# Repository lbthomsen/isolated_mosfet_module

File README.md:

# isolated_mosfet_module
Isolated MOSFET Module

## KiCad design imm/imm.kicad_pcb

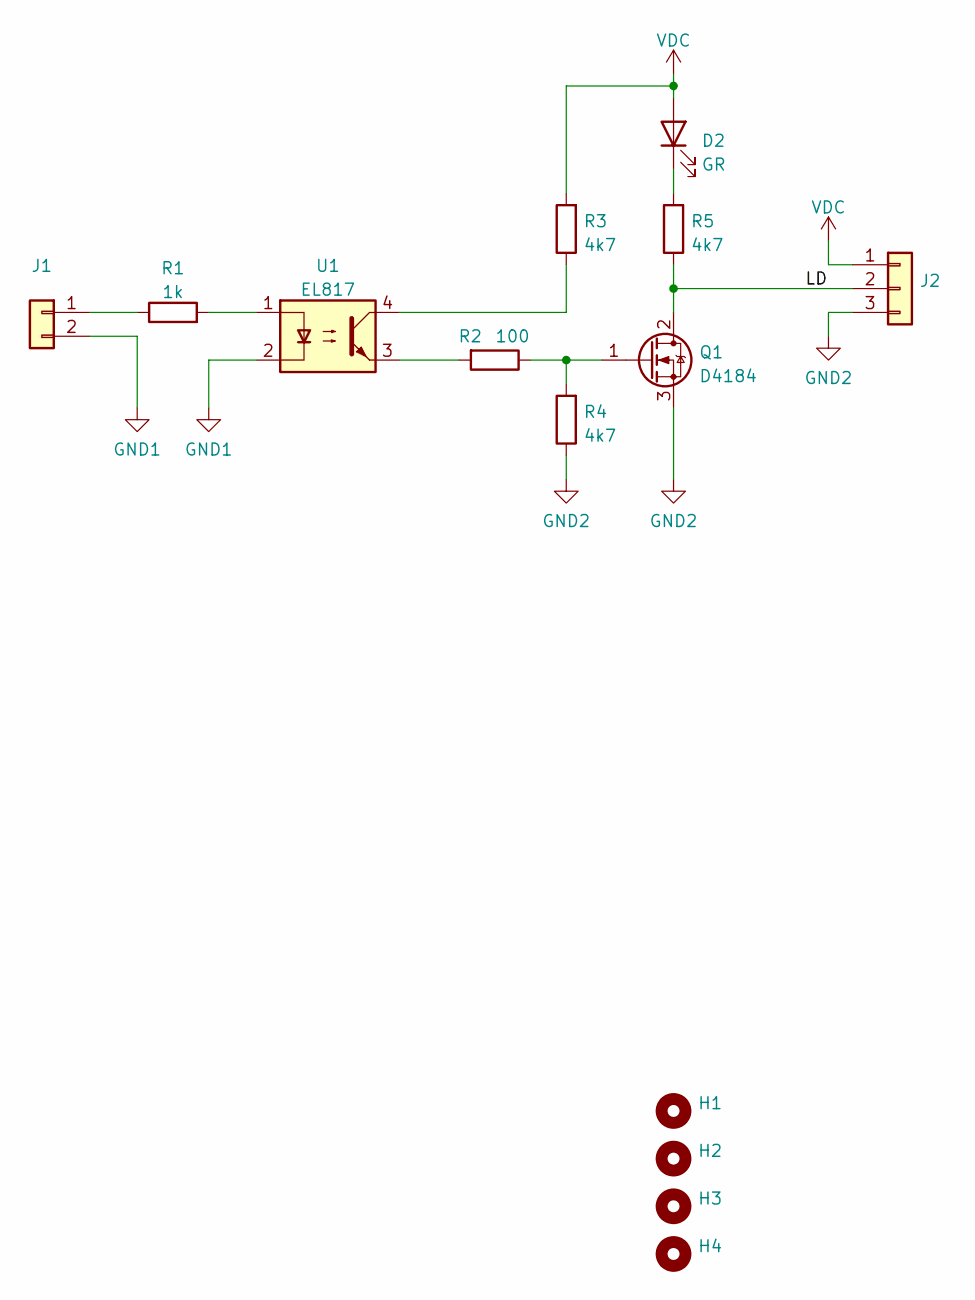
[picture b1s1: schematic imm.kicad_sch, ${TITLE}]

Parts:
D2: GR; LED_0603_1608Metric; LCSC C72043
H1, H2, H3, H4: MountingHole; MountingHole_2.2mm_M2_DIN965
J1: Conn_01x02; PinHeader_1x02_P2.54mm_Vertical
J2: Conn_01x03; PinHeader_1x03_P2.54mm_Vertical
Q1: D4184; TO-252-2; LCSC C99124
R1: 1k; R_0603_1608Metric; LCSC C21190
R2: 100; R_0603_1608Metric; LCSC C22775
R3, R4, R5: 4k7; R_0603_1608Metric; LCSC C23162
U1: EL817; SMDIP-4_W9.53mm; LCSC C106900

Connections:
/LD: J2.2, Q1.2 (D), R5.1
GND1: J1.2, U1.2
GND2: J2.3, Q1.3 (S), R4.1
unnamed: D2.1 (K), R5.2
unnamed: J1.1, R1.1
unnamed: Q1.1 (G), R2.1, R4.2
unnamed: R1.2, U1.1
unnamed: R2.2, U1.3
unnamed: R3.1, U1.4
VDC: D2.2 (A), J2.1, R3.2

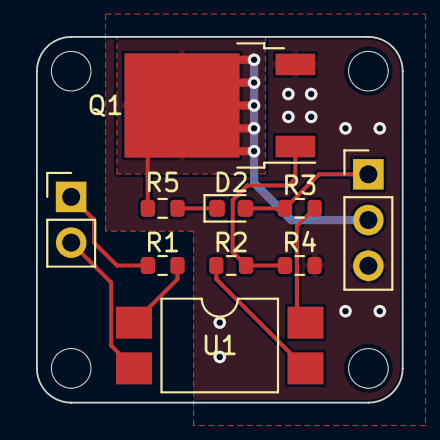
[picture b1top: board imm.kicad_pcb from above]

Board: 2 copper layers, 20.3 x 20.3 mm, 14 parts (0 on the bottom side), 10 nets.

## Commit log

2022-06-19 Hmmmm
2022-06-20 Hmmm
2022-06-20 Tweaking
